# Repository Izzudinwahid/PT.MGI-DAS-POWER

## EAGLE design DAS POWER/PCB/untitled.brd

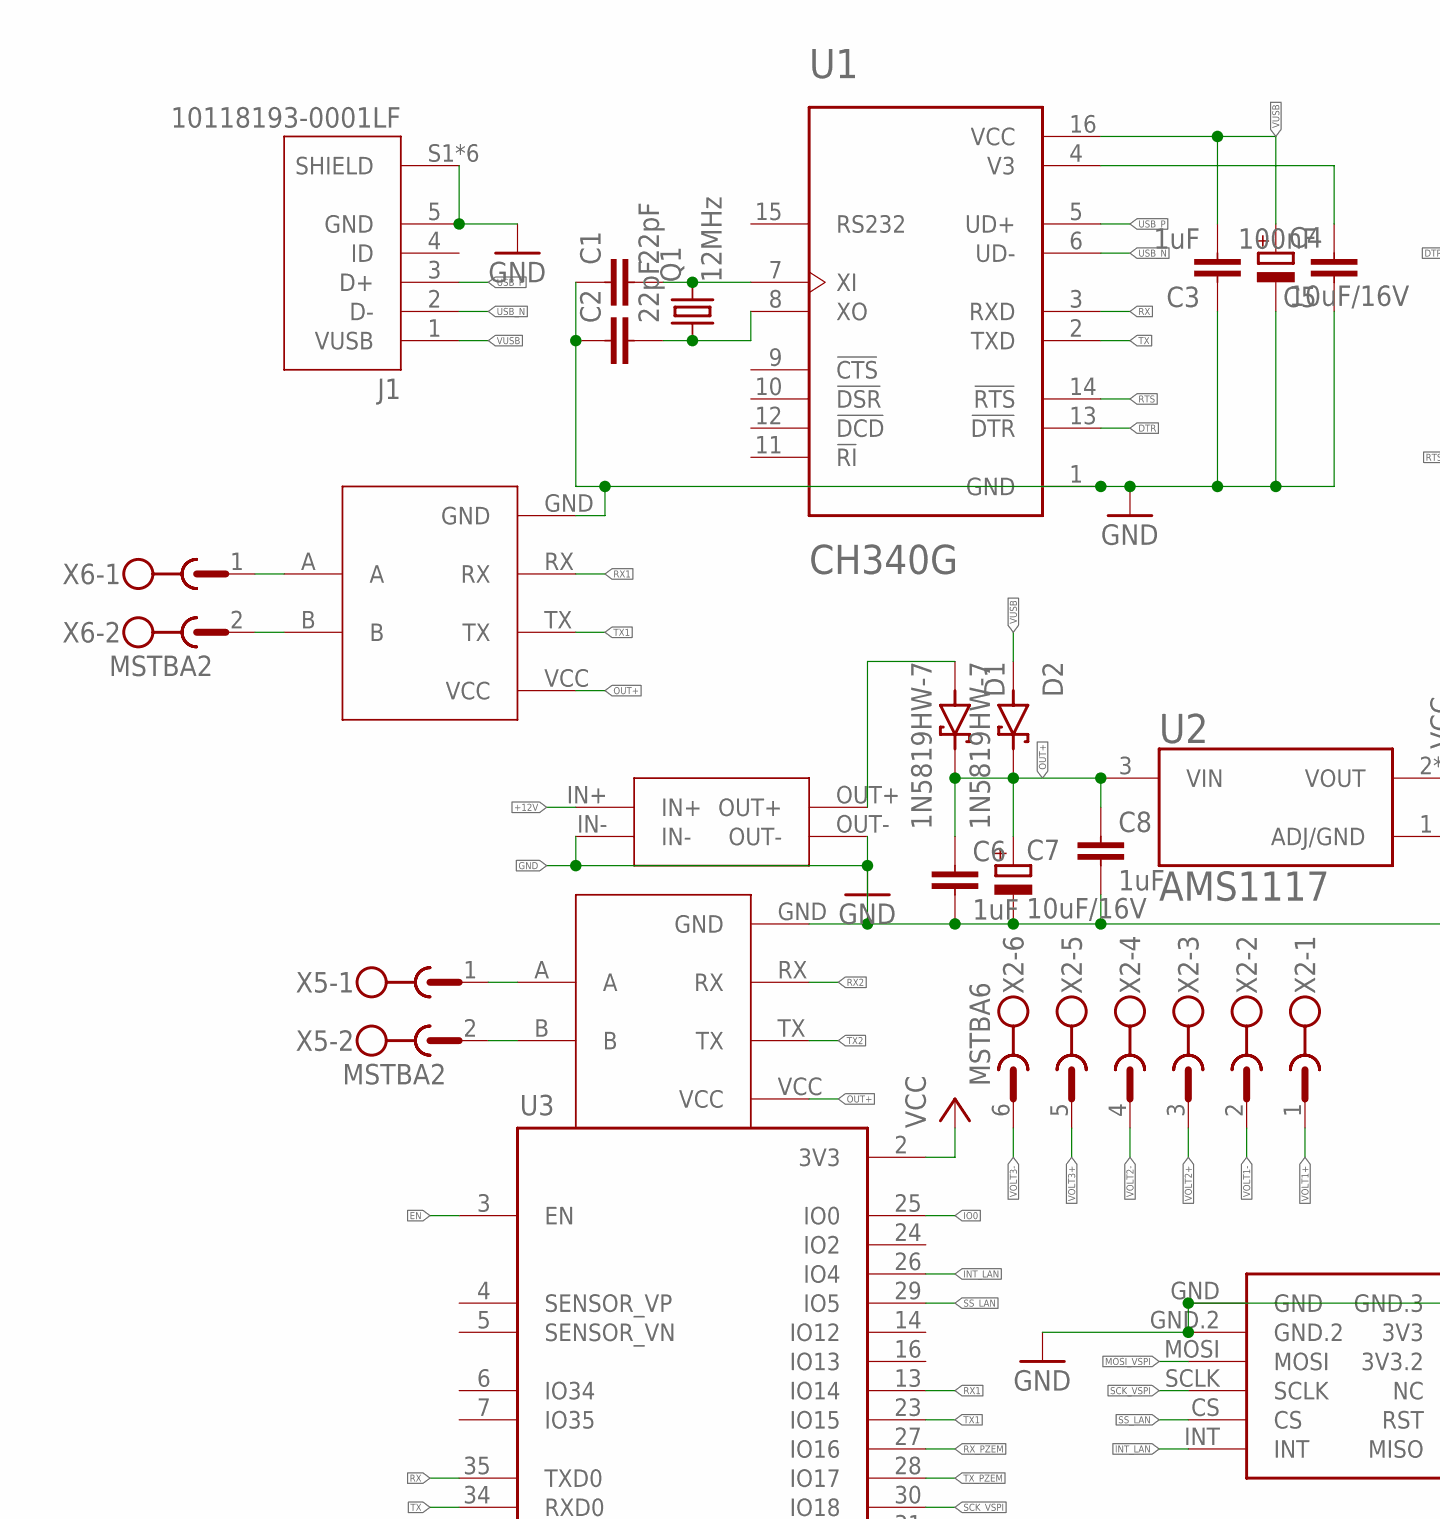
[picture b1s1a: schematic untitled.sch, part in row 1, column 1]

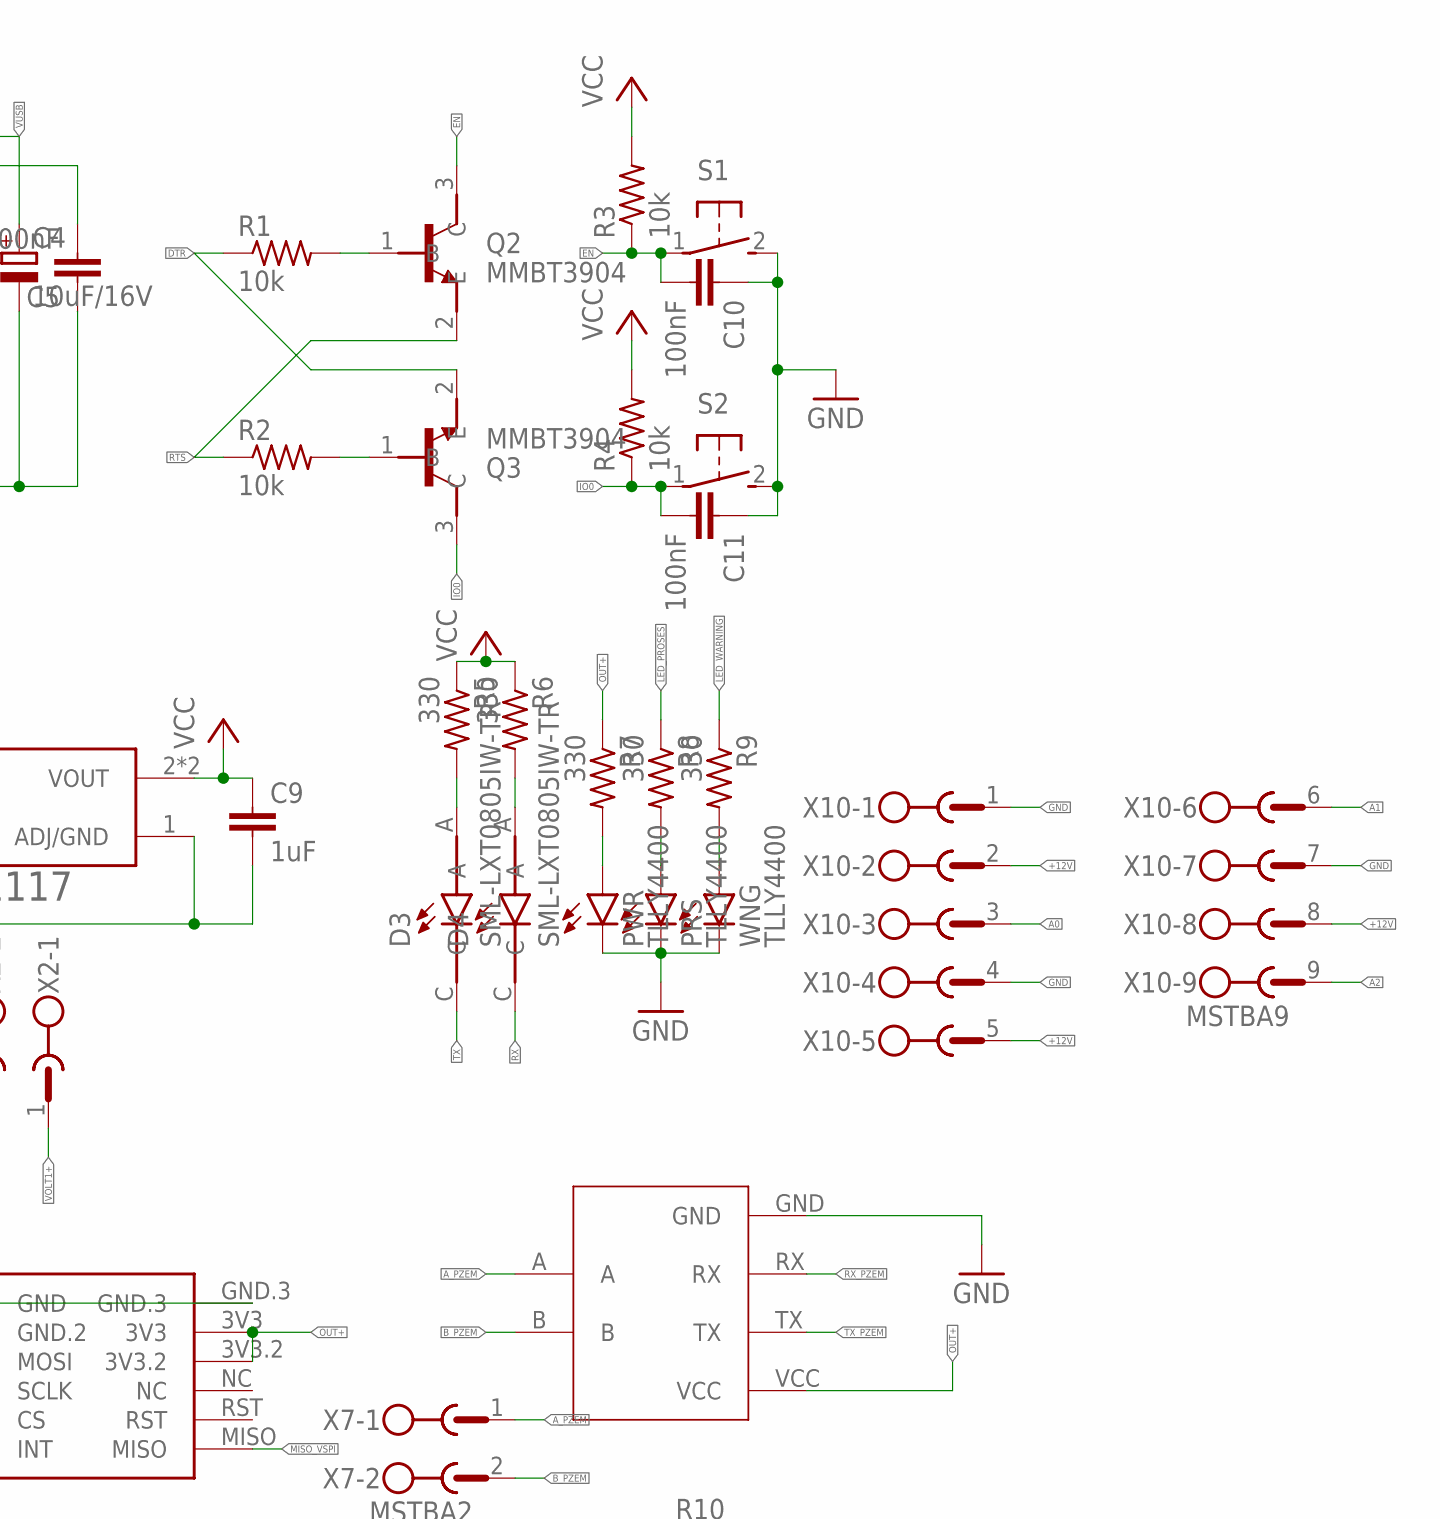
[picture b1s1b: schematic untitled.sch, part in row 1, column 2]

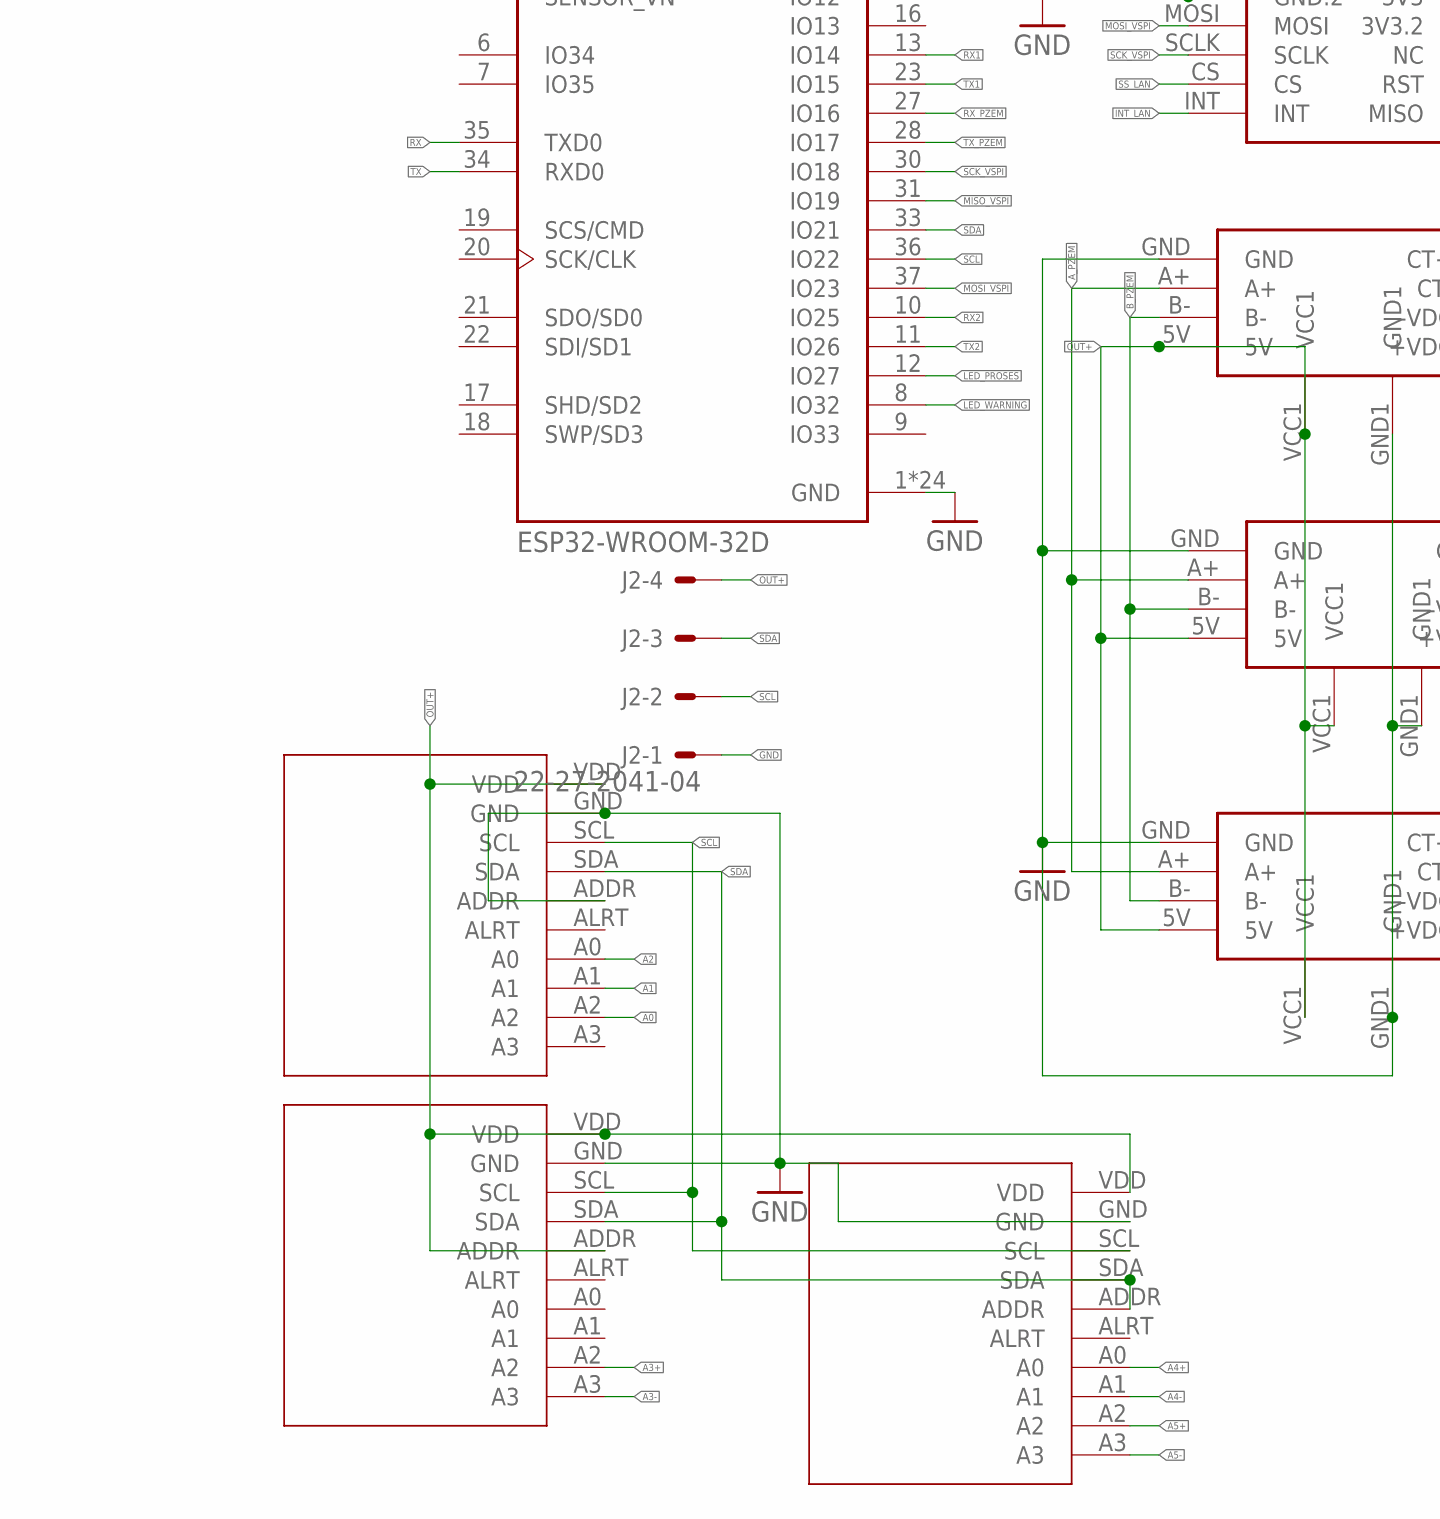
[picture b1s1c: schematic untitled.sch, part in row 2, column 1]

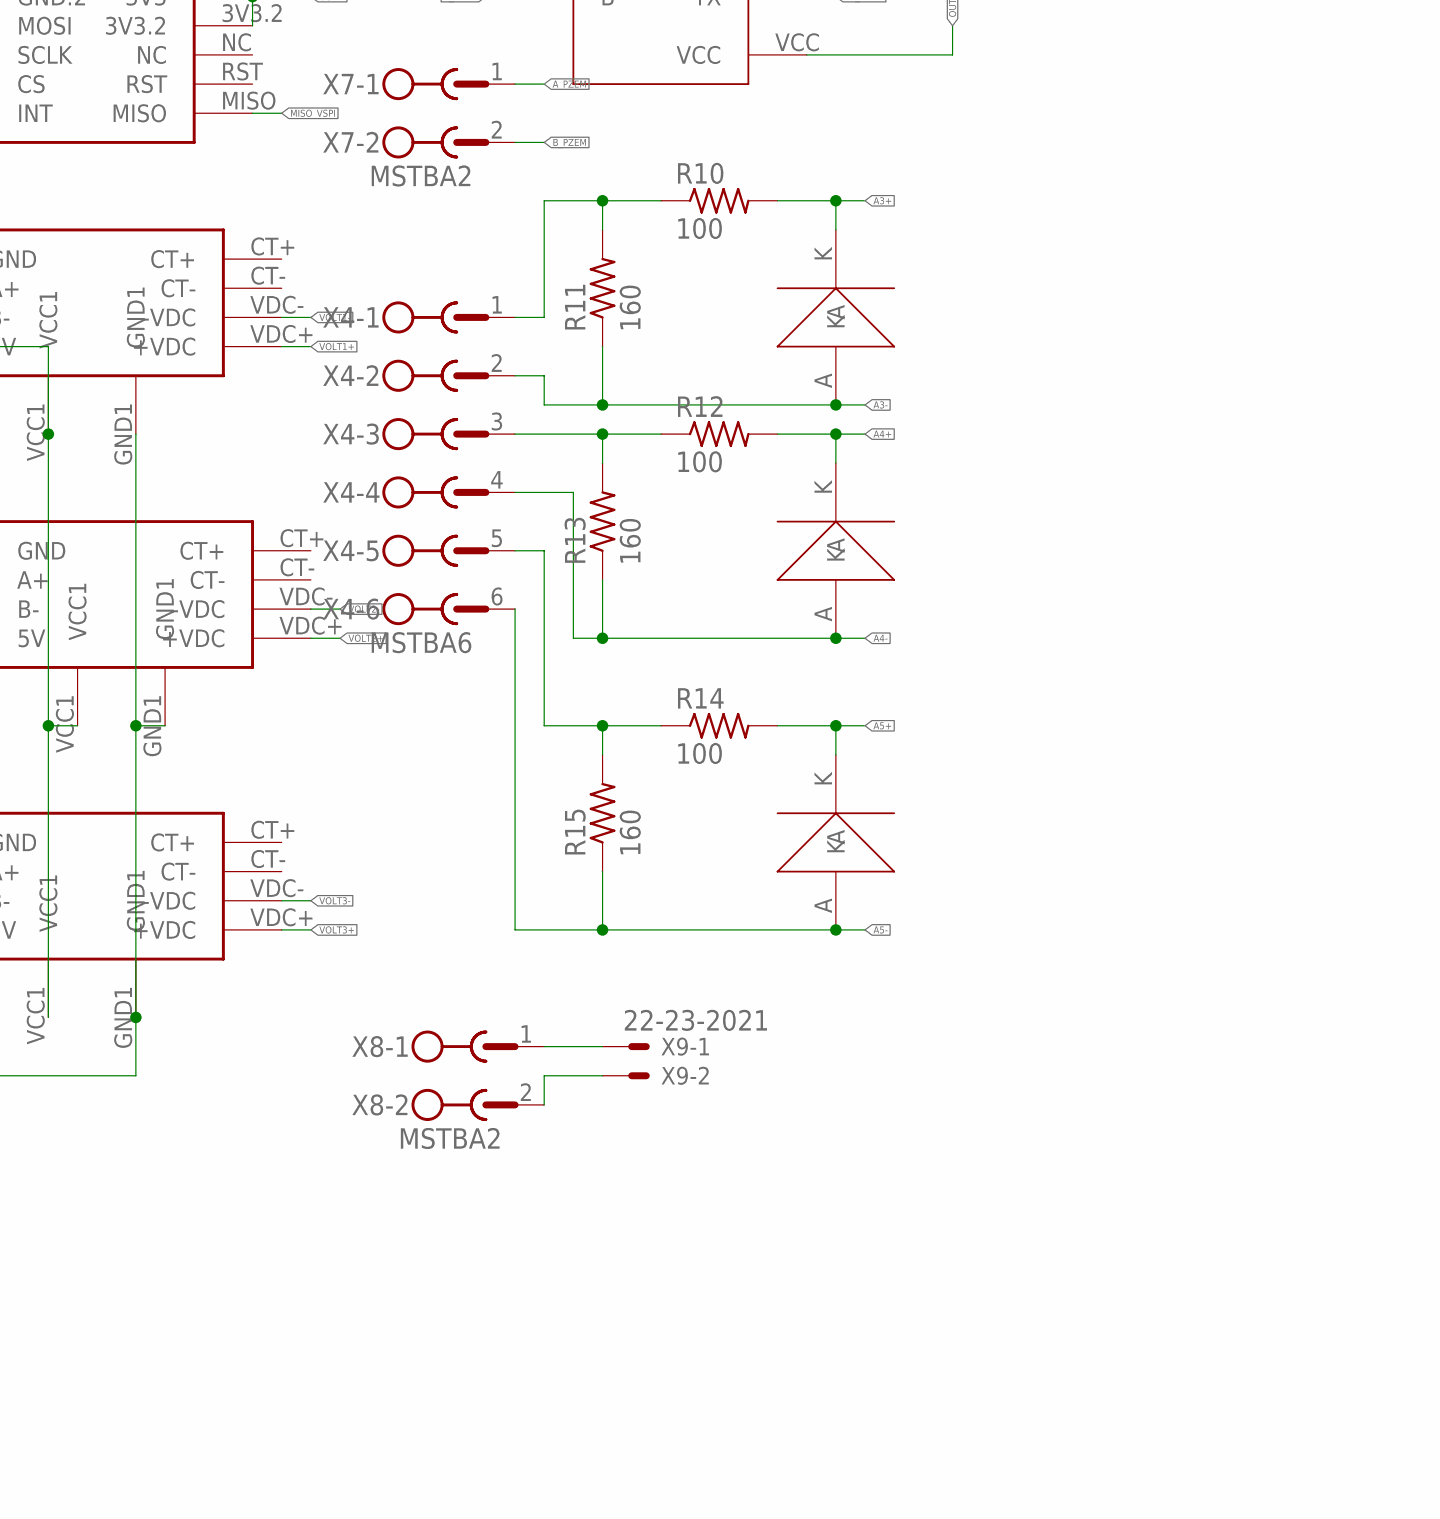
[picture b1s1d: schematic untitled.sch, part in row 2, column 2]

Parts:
ADS1, ADS2, ADS3: ADS1115
C1, C2: 22pF; C0805K
C3, C6, C8, C9: 1uF; C0805K
C4, C7: 10uF/16V; 153CLV-0505
C5, C10, C11: 100nF; C0805K
D1, D2: 1N5819HW-7; SOD3715X145N
D3, D4: SML-LXT0805IW-TR; LEDC2012X120N
J1: 10118193-0001LF; FCI_10118193-0001LF
J2: 22-27-2041-04; 6410-04
MINI1: MINI560
PRS: TLLY4400; LED3MM
PWR: TLLY4400; LED3MM
PZEM-DC1, PZEM-DC2, PZEM-DC3: PZEM-DC
Q1: 12MHz; SM49
Q2, Q3: MMBT3904; SOT95P240X120-3N
R1, R2, R3, R4: 10k; M0805
R5, R6, R7, R8, R9: 330; M0805
R10, R12, R14: 100; M0805
R11, R13, R15: 160; M0805
S1, S2: 31-XX; B3F-31XX
TTL-RS1, TTL-RS2, TTL-RS3: TTL-RS485
U1: CH340G; SOIC127P600X180-16N
U2: AMS1117; SOT229P700X180-4N
U3: ESP32-WROOM-32D; MODULE_ESP32-WROOM-32D
U$1: MINI_W5500
WNG: TLLY4400; LED3MM
X2, X4: MSTBA6
X5, X6, X7, X8: MSTBA2
X9: 22-23-2021
X10: MSTBA9
ZENER3V1: 3v3; DIO_LL4148
ZENER3V2, ZENER3V3: ZENER3V3; DIO_LL4148

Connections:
+12V: MINI1.IN+, X10.2, X10.5, X10.8
A0: ADS1.A2, X10.3
A1: ADS1.A1, X10.6
A2: ADS1.A0, X10.9
A3+: ADS2.A2, R10.2, ZENER3V1.K
A3-: ADS2.A3, R11.1, X4.2, ZENER3V1.A
A4+: ADS3.A0, R12.2, ZENER3V2.K
A4-: ADS3.A1, R13.1, X4.4, ZENER3V2.A
A5+: ADS3.A2, R14.2, ZENER3V3.K
A5-: ADS3.A3, R15.1, X4.6, ZENER3V3.A
A_PZEM: PZEM-DC1.A+, PZEM-DC2.A+, PZEM-DC3.A+, TTL-RS1.A, X7.1
B_PZEM: PZEM-DC1.B-, PZEM-DC2.B-, PZEM-DC3.B-, TTL-RS1.B, X7.2
DTR: Q3.2 (E), R1.1, U1.13 (!DTR)
EN: C10.2, Q2.3 (C), R3.1, S1.1, U3.3 (EN)
GND: ADS1.ADDR, ADS1.GND, ADS2.GND, ADS3.GND, C1.1, C2.1, C3.1, C4.-, C5.1, C6.2, C7.-, C8.2, C9.2, C10.1, C11.1, J1.5 (GND), J1.S1 (SHIELD), J1.S2 (SHIELD), J1.S3 (SHIELD), J1.S4 (SHIELD), J1.S5 (SHIELD), J1.S6 (SHIELD), J2.1, MINI1.IN-, MINI1.OUT-, PRS.K (C), PWR.K (C), PZEM-DC1.GND, PZEM-DC1.GND1, PZEM-DC2.GND, PZEM-DC2.GND1, PZEM-DC3.GND, PZEM-DC3.GND1, S1.2 (S), S2.2 (S), TTL-RS1.GND, TTL-RS2.GND, TTL-RS3.GND, U1.1 (GND), U2.1 (ADJ/GND), U3.1 (GND), U3.15 (GND), U3.38 (GND), U3.39_1 (GND), U3.39_2 (GND), U3.39_3 (GND), U3.39_4 (GND), U3.39_5 (GND), U3.39_6 (GND), U3.39_7 (GND), U3.39_8 (GND), U3.39_9 (GND), U3.39_10 (GND), U3.39_11 (GND), U3.39_12 (GND), U3.39_13 (GND), U3.39_14 (GND), U3.39_15 (GND), U3.39_16 (GND), U3.39_17 (GND), U3.39_18 (GND), U3.39_19 (GND), U3.39_20 (GND), U3.39_21 (GND), U$1.GND, U$1.GND.2, U$1.GND.3, WNG.K (C), X10.1, X10.4, X10.7
INT_LAN: U3.26 (IO4), U$1.INT
IO0: C11.2, Q3.3 (C), R4.1, S2.1, U3.25 (IO0)
LED_PROSES: R8.1, U3.12 (IO27)
LED_WARNING: R9.1, U3.8 (IO32)
MISO_VSPI: U3.31 (IO19), U$1.MISO
MOSI_VSPI: U3.37 (IO23), U$1.MOSI
unnamed: C1.2, Q1.2, U1.7 (XI)
unnamed: C2.2, Q1.1, U1.8 (XO)
unnamed: C5.2, U1.4 (V3)
unnamed: Q2.1 (B), R1.2
unnamed: Q3.1 (B), R2.2
unnamed: D1.A, MINI1.OUT+
unnamed: R10.1, R11.2, X4.1
unnamed: D3.A, R5.2
unnamed: D4.A, R6.2
unnamed: PWR.A, R7.2
unnamed: PRS.A, R8.2
unnamed: R9.2, WNG.A
unnamed: TTL-RS2.A, X6.1
unnamed: TTL-RS2.B, X6.2
unnamed: X8.1, X9.1
unnamed: X8.2, X9.2
unnamed: R12.1, R13.2, X4.3
unnamed: TTL-RS3.A, X5.1
unnamed: TTL-RS3.B, X5.2
unnamed: R14.1, R15.2, X4.5
OUT+: ADS1.VDD, ADS2.ADDR, ADS2.VDD, ADS3.VDD, C6.1, C7.+, C8.1, D1.C (K), D2.C (K), J2.4, PZEM-DC1.5V, PZEM-DC1.VCC1, PZEM-DC2.5V, PZEM-DC2.VCC1, PZEM-DC3.5V, PZEM-DC3.VCC1, R7.1, TTL-RS1.VCC, TTL-RS2.VCC, TTL-RS3.VCC, U2.3 (VIN), U$1.3V3, U$1.3V3.2
RTS: Q2.2 (E), R2.1, U1.14 (!RTS)
RX: D4.C, U1.3 (RXD), U3.35 (TXD0)
RX1: TTL-RS2.RX, U3.13 (IO14)
RX2: TTL-RS3.RX, U3.10 (IO25)
RX_PZEM: TTL-RS1.RX, U3.27 (IO16)
SCK_VSPI: U3.30 (IO18), U$1.SCLK
SCL: ADS1.SCL, ADS2.SCL, ADS3.SCL, J2.2, U3.36 (IO22)
SDA: ADS1.SDA, ADS2.SDA, ADS3.ADDR, ADS3.SDA, J2.3, U3.33 (IO21)
SS_LAN: U3.29 (IO5), U$1.CS
TX: D3.C, U1.2 (TXD), U3.34 (RXD0)
TX1: TTL-RS2.TX, U3.23 (IO15)
TX2: TTL-RS3.TX, U3.11 (IO26)
TX_PZEM: TTL-RS1.TX, U3.28 (IO17)
USB_N: J1.2 (D-), U1.6 (UD-)
USB_P: J1.3 (D+), U1.5 (UD+)
VCC: C9.1, R3.2, R4.2, R5.1, R6.1, U2.2 (VOUT), U2.4 (VOUT), U3.2 (3V3)
VOLT1+: PZEM-DC1.VDC+ (+VDC), X2.1
VOLT1-: PZEM-DC1.VDC- (-VDC), X2.2
VOLT2+: PZEM-DC2.VDC+ (+VDC), X2.3
VOLT2-: PZEM-DC2.VDC- (-VDC), X2.4
VOLT3+: PZEM-DC3.VDC+ (+VDC), X2.5
VOLT3-: PZEM-DC3.VDC- (-VDC), X2.6
VUSB: C3.2, C4.+, D2.A, J1.1 (VUSB), U1.16 (VCC)

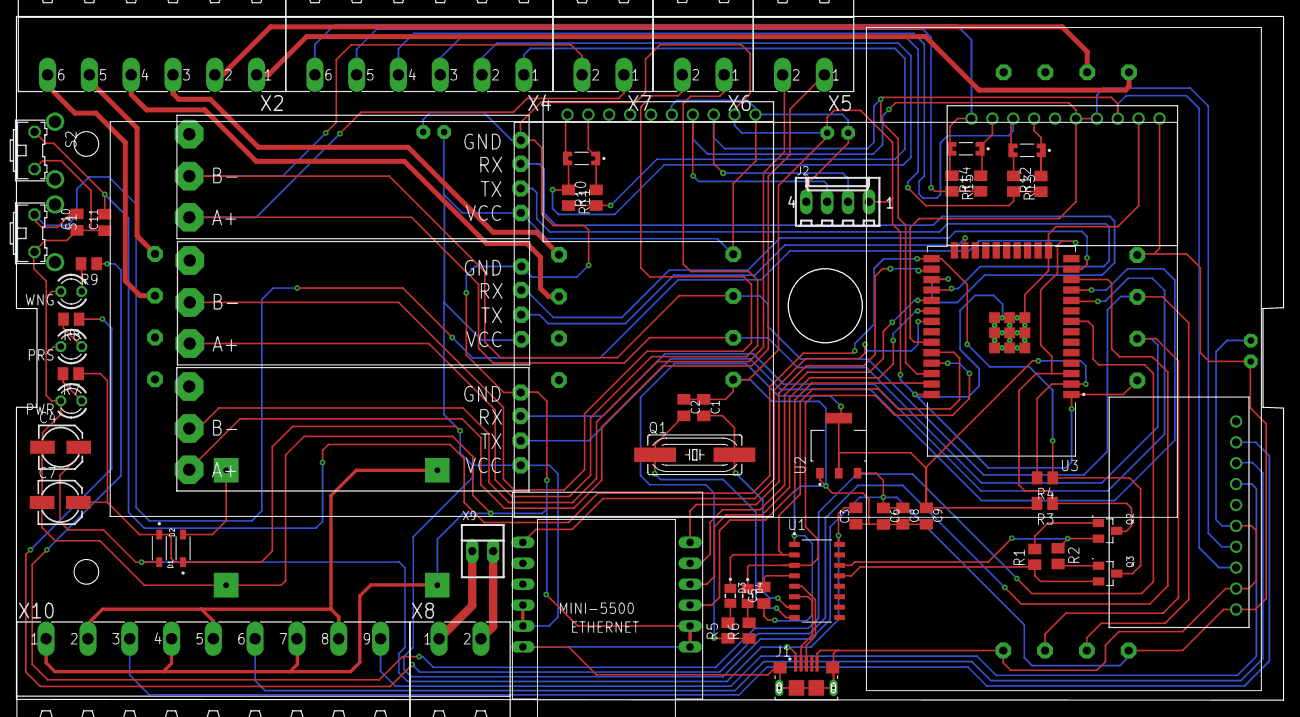
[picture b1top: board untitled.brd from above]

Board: 2 copper layers, 154.0 x 83.1 mm, 65 parts (1 on the bottom side), 65 nets.

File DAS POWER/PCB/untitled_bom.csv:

Comment,Designator,Footprint,LCSC Part #
,ADS1,ADS1115,
,ADS2,ADS1115,
,ADS3,ADS1115,
,S1,B3F-31XX,
,S2,B3F-31XX,
,ZENER3V2,DIO_LL4148,
,ZENER3V3,DIO_LL4148,
,MINI1,MINI560,
,PZEM-DC1,PZEM-DC,
,PZEM-DC2,PZEM-DC,
,PZEM-DC3,PZEM-DC,
,TTL-RS1,TTL-RS485,
,TTL-RS2,TTL-RS485,
,TTL-RS3,TTL-RS485,
1N5819HW-7,D1 D2,SOD3715X145N,
1uF,C3 C6 C8 C9,C0805K,
3v3,ZENER3V1,DIO_LL4148,
10k,R1 R2 R3 R4,M0805,
10uF/16V,C4 C7,153CLV-0505,
12MHz,Q1,SM49,
22-23-2021,X9,22-23-2021,
22-27-2041-04,J2,6410-04,
22pF,C1 C2,C0805K,
100,R10 R12 R14,M0805,
100nF,C5 C10 C11,C0805K,
160,R11 R13 R15,M0805,
330,R5 R6 R7 R8 R9,M0805,
10118193-0001LF,J1,FCI_10118193-0001LF,
AMS1117,U2,SOT229P700X180-4N,
CH340G,U1,SOIC127P600X180-16N,
ESP32-WROOM-32D,U3,MODULE_ESP32-WROOM-32D,
MINI_W5500,U$1,MINI_W5500,
MMBT3904,Q2 Q3,SOT95P240X120-3N,
MSTBA2,X5 X6 X7 X8,MSTBA2,
MSTBA6,X2 X4,MSTBA6,
MSTBA9,X10,MSTBA9,
SML-LXT0805IW-TR,D3 D4,LEDC2012X120N,
TLLY4400,PRS PWR WNG,LED3MM,

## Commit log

2023-02-16 Das Power 16/02/2023
2023-02-21 revisi final tanggal 21/02.2023
2023-05-26 PCB DAS POWER
2023-05-31 fix PCB
